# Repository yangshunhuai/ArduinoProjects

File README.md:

# ArduinoProjects
我的Arduino项目，包括硬件测试和其它程序。

## 正在进行的项目

* [ESP8266Watch](https://github.com/yangshunhuai/ESP8266Watch)
  
  由于本项目较大，单独设仓库存放。

* [TomatoClock](https://github.com/yangshunhuai/ArduinoProjects/tree/main/projects/TomatoClock)

## 鸽了的项目

* [Drinker](https://github.com/yangshunhuai/ArduinoProjects/tree/main/projects/Drinker)

  鸽的原因：水泵的管子不见了，材料没了。

## 完成的项目
* [CPUMemMonitor](https://github.com/yangshunhuai/ArduinoProjects/tree/main/projects/CPUMemMonitor)
* [simple-clock-with-dht](https://github.com/yangshunhuai/ArduinoProjects/tree/main/projects/simple-clock-with-dht)
* [simple-clock](https://github.com/yangshunhuai/ArduinoProjects/tree/main/projects/simple-clock)

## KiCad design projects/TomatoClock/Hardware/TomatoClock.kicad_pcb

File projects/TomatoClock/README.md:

# TomatoClock

本项目已迁至新址：[https://github.com/yangshunhuai/TomatoClock](https://github.com/yangshunhuai/TomatoClock)。

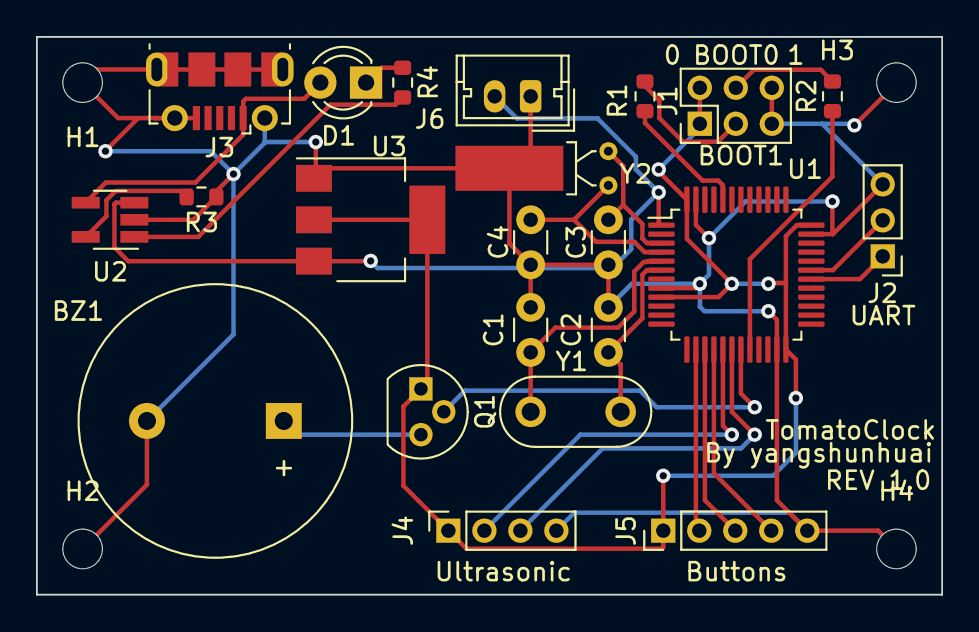
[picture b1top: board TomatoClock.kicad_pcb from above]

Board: 2 copper layers, 50.3 x 31.0 mm, 26 parts (0 on the bottom side), 24 nets.

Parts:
BZ1: Buzzer; Buzzer_15x7.5RM7.6
C1, C2, C3, C4: 22pF; C_Disc_D3.0mm_W1.6mm_P2.50mm
D1: Charge; LED_D3.0mm
H1, H2, H3, H4: hole; MountingHole_2.2mm_M2
J1: Boot; PinHeader_2x03_P2.00mm_Vertical
J2: UART; PinHeader_1x03_P2.00mm_Vertical
J3: USB_B_Micro; USB_Micro-B_Molex-105017-0001
J4: Ultrasonic; PinSocket_1x04_P2.00mm_Vertical
J5: Buttons; PinHeader_1x05_P2.00mm_Vertical
J6: Battery; Molex_Micro-Latch_53253-0270_1x02_P2.00mm_Vertical
Q1: S9014; TO-92
R1, R2: 100k; R_0603_1608Metric
R3, R4: 10k; R_0603_1608Metric
U1: STM32F103C8T6; LQFP-48_7x7mm_P0.5mm
U2: WS4518E; SOT-23-5_HandSoldering
U3: AP1117-33; SOT-223-3_TabPin2
Y1: 8MHz; Resonator-2Pin_W8.0mm_H3.5mm
Y2: 32.768kHz; Crystal_DS26_D2.0mm_L6.0mm_Horizontal_1EP_style1

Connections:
+3V3: J1.1, J1.2, J4.1, J5.1, Q1.1, U1.9, U1.24, U1.36, U1.48, U3.2
+BATT: J6.2, U1.1, U2.3, U3.3
BOOT0: R1.2, U1.44
BOOT1: R2.1, U1.20
BUZZER: Q1.2, U1.19
GND: BZ1.2, C1.2, C2.2, C3.2, C4.2, H1.1, H2.1, H3.1, H4.1, J1.5, J1.6, J2.3, J3.5, J3.6, J4.4, J5.5, J6.1, R3.1, U1.8, U1.23, U1.35, U1.47, U2.2, U3.1, Y2.3
LEFT: J5.2, U1.14
MIDDLE: J5.3, U1.15
unnamed: BZ1.1, Q1.3
unnamed: C1.1, U1.5, Y1.1
unnamed: C2.1, U1.6, Y1.2
unnamed: C3.1, U1.3, Y2.1
unnamed: C4.1, U1.4, Y2.2
unnamed: D1.1, R4.1
unnamed: J1.3, R1.1
unnamed: J1.4, R2.2
unnamed: J2.1, U1.30
unnamed: J2.2, U1.31
unnamed: R3.2, U2.5
unnamed: R4.2, U2.1
RIGHT: J5.4, U1.16
US_ECHO: J4.3, U1.18
US_TRIG: J4.2, U1.17
VBUS: D1.2, J3.1, U2.4

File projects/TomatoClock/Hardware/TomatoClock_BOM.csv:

"Comment","Description","Designator","Footprint","LibRef","Pins","Quantity","PartNumber","url",
"100k","desc","R1,R2,","R_0603_1608Metric","libref","2","2","","",
"10k","desc","R3,R4,","R_0603_1608Metric","libref","2","2","","",
"STM32F103C8T6","desc","U1,","LQFP-48_7x7mm_P0.5mm","libref","48","1","","",
"WS4518E","desc","U2,","SOT-23-5_HandSoldering","libref","5","1","","",
"AP1117-33","desc","U3,","SOT-223-3_TabPin2","libref","4","1","","",
"Through Hole Items ",
"22pF","desc","C1,C2,C3,C4,","C_Disc_D3.0mm_W1.6mm_P2.50mm","libref","2","4","","",
"Charge","desc","D1,","LED_D3.0mm","libref","2","1","","",
"hole","desc","H1,H2,H3,H4,","MountingHole_2.2mm_M2","libref","1","4","","",
"Boot","desc","J1,","PinHeader_2x03_P2.00mm_Vertical","libref","6","1","","",
"UART","desc","J2,","PinHeader_1x03_P2.00mm_Vertical","libref","3","1","","",
"USB_B_Micro","desc","J3,","USB_Micro-B_Molex-105017-0001","libref","13","1","","",
"Ultrasonic","desc","J4,","PinSocket_1x04_P2.00mm_Vertical","libref","4","1","","",
"Buttons","desc","J5,","PinHeader_1x05_P2.00mm_Vertical","libref","5","1","","",
"Battery","desc","J6,","Molex_Micro-Latch_53253-0270_1x02_P2.00mm_Vertical","libref","2","1","","",
"S9014","desc","Q1,","TO-92","libref","3","1","","",
"8MHz","desc","Y1,","Resonator-2Pin_W8.0mm_H3.5mm","libref","2","1","","",
"32.768kHz","desc","Y2,","Crystal_DS26_D2.0mm_L6.0mm_Horizontal_1EP_style1","libref","3","1","","",
"Buzzer","desc","BZ1,","Buzzer_15x7.5RM7.6","libref","2","1","","",

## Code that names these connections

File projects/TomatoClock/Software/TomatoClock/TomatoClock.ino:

/*
 * TomatoClock Main Program
 * Wiring: See hardware schematics
 * Author: yangshunhuai
 * Revision: 1.0
 */

#include <U8g2lib.h>
#include <OneButton.h>
#include <SoftwareSerial.h>
#include <ThreeWire.h>
#include <RtcDS1302.h>
#include "tones.h"

// Device pins
#define BTNLEFT    2
#define BTNENTER   3
#define BTNRIGHT   4
#define BUZZER     10
#define US_TRIG    5
#define US_ECHO    6
#define BT_SER_TX  7
#define BT_SER_RX  8
#define DS1302_CLK A0
#define DS1302_DAT A1
#define DS1302_RST A2
String BT_NAME =   "TomatoClock";

// Devices
U8G2_SSD1306_128X64_NONAME_F_HW_I2C u8g2(U8G2_R0, /* reset=*/ U8X8_PIN_NONE);
OneButton btnleft(BTNLEFT, false);
OneButton btnenter(BTNENTER, false);
OneButton btnright(BTNRIGHT, false);
ThreeWire mywire(DS1302_DAT, DS1302_CLK, DS1302_RST);
RtcDS1302<ThreeWire> rtc(mywire);
SoftwareSerial btser(BT_SER_TX, BT_SER_RX);

void setup() {
  // Configure pins
  pinMode(BUZZER, OUTPUT);
  pinMode(US_TRIG, OUTPUT);
  pinMode(US_ECHO, INPUT);
  // Configure devices
  u8g2.begin();
  rtc.Begin();
  btser.begin(9600);
  btser.print("AT+NAME" + BT_NAME + "\r\n");
}

void loop() {
  // put your main code here, to run repeatedly:
}

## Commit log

2021-06-27 Add a lot of programs
2021-06-27 remove vscode config
2021-06-28 CPUMemMonitor: Add client and server program
2021-06-30 hardware-tests/Infrared: Improve code quality
2021-06-30 CPUMemMonitor: Make it possible to show the blocks in a more precise way; code quality
2021-07-01 Drinker: Create project & MFRC522 module test
2021-07-02 Rename README.md to README_en.md
2021-07-03 README: add CPUMemMonitor proj
2021-07-04 Drinker: Update sketch
2021-07-09 update gitignote
2021-07-10 Sketches: Lots of sketch update
    This update includes adding sketch for simple-clock, simple-clock-with-dht.
    Added Lift project.
    Updated README.
2021-07-11 gitignore: Update gitignore
2021-08-08 I2CScanner: Create I2CScanner
2021-08-08 Lift: Remove lift project
2021-08-10 PrototypeShield: Add PrototypeShield circuit sketch
2021-08-10 Doorbell: Add Doorbell sketch
2021-10-29 TomatoClock: Update code
2021-11-15 TomatoClock: Add project TomatoClock
2021-11-17 TomatoClock: Update hardware schematics
2021-11-21 TomatoClock: Update hardware
2021-11-22 TomatoClock: Software update due to hardware update
2021-11-26 TomatoClock: Update PCB footprints and schematics
2021-11-26 TomatoClock: Update program
2021-11-28 TomatoClock: Update software
2021-11-28 TomatoClock: Change U1 from ATmega328p to STM32F103C8T6; Add power management citcuit; Update PCB
2021-12-05 TomatoClock: Update README
2021-12-05 TomatoClock: Update PCB and Gerber files
2021-12-07 TomatoClock: Update C1-C4 from TH to SMD
2021-12-18 TomatoClock: All the files moved to https://github.com/yangshunhuai/TomatoClock
2022-01-28 timer: Add timer project to ArduinoProjects
